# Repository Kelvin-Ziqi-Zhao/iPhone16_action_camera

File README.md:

# iPhone camera to IPEX coaxial cabel

Extend iPhone 16 Pro/Max wide camera FPC, using IPEX 20454 20pin

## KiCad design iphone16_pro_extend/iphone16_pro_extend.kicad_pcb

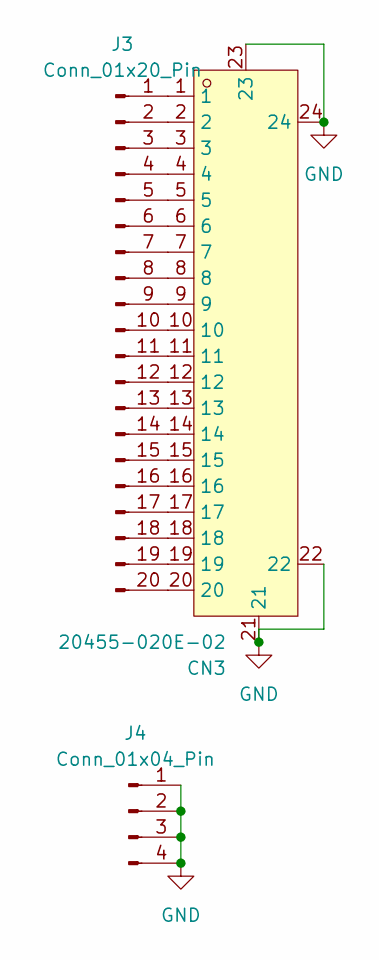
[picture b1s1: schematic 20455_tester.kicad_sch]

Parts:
CN3: 20455-020E-02; CONN-SMD_20P-P0.50_I-PEX_20455-020E-02; LCSC Part C7527729
J3: Conn_01x20_Pin; PinSocket_1x20_P2.54mm_Vertical
J4: Conn_01x04_Pin; PinSocket_1x04_P2.54mm_Vertical

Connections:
GND: CN3.21, CN3.22, CN3.23, CN3.24, J4.1, J4.2, J4.3, J4.4; also elsewhere on the board
unnamed: CN3.1, J3.1
unnamed: CN3.2, J3.2
unnamed: CN3.3, J3.3
unnamed: CN3.4, J3.4
unnamed: CN3.5, J3.5
unnamed: CN3.6, J3.6
unnamed: CN3.7, J3.7
unnamed: CN3.8, J3.8
unnamed: CN3.9, J3.9
unnamed: CN3.10, J3.10
unnamed: CN3.11, J3.11
unnamed: CN3.12, J3.12
unnamed: CN3.13, J3.13
unnamed: CN3.14, J3.14
unnamed: CN3.15, J3.15
unnamed: CN3.16, J3.16
unnamed: CN3.17, J3.17
unnamed: CN3.18, J3.18
unnamed: CN3.19, J3.19
unnamed: CN3.20, J3.20

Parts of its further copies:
CN4: 20455-020E-02; CONN-SMD_20P-P0.50_I-PEX_20455-020E-02; LCSC Part C7527729
J5: Conn_01x20_Pin; PinSocket_1x20_P2.54mm_Vertical
J6: Conn_01x04_Pin; PinSocket_1x04_P2.54mm_Vertical

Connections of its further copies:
GND: CN4.21, CN4.22, CN4.23, CN4.24, J6.1, J6.2, J6.3, J6.4; also elsewhere on the board
unnamed: CN4.1, J5.1
unnamed: CN4.2, J5.2
unnamed: CN4.3, J5.3
unnamed: CN4.4, J5.4
unnamed: CN4.5, J5.5
unnamed: CN4.6, J5.6
unnamed: CN4.7, J5.7
unnamed: CN4.8, J5.8
unnamed: CN4.9, J5.9
unnamed: CN4.10, J5.10
unnamed: CN4.11, J5.11
unnamed: CN4.12, J5.12
unnamed: CN4.13, J5.13
unnamed: CN4.14, J5.14
unnamed: CN4.15, J5.15
unnamed: CN4.16, J5.16
unnamed: CN4.17, J5.17
unnamed: CN4.18, J5.18
unnamed: CN4.19, J5.19
unnamed: CN4.20, J5.20

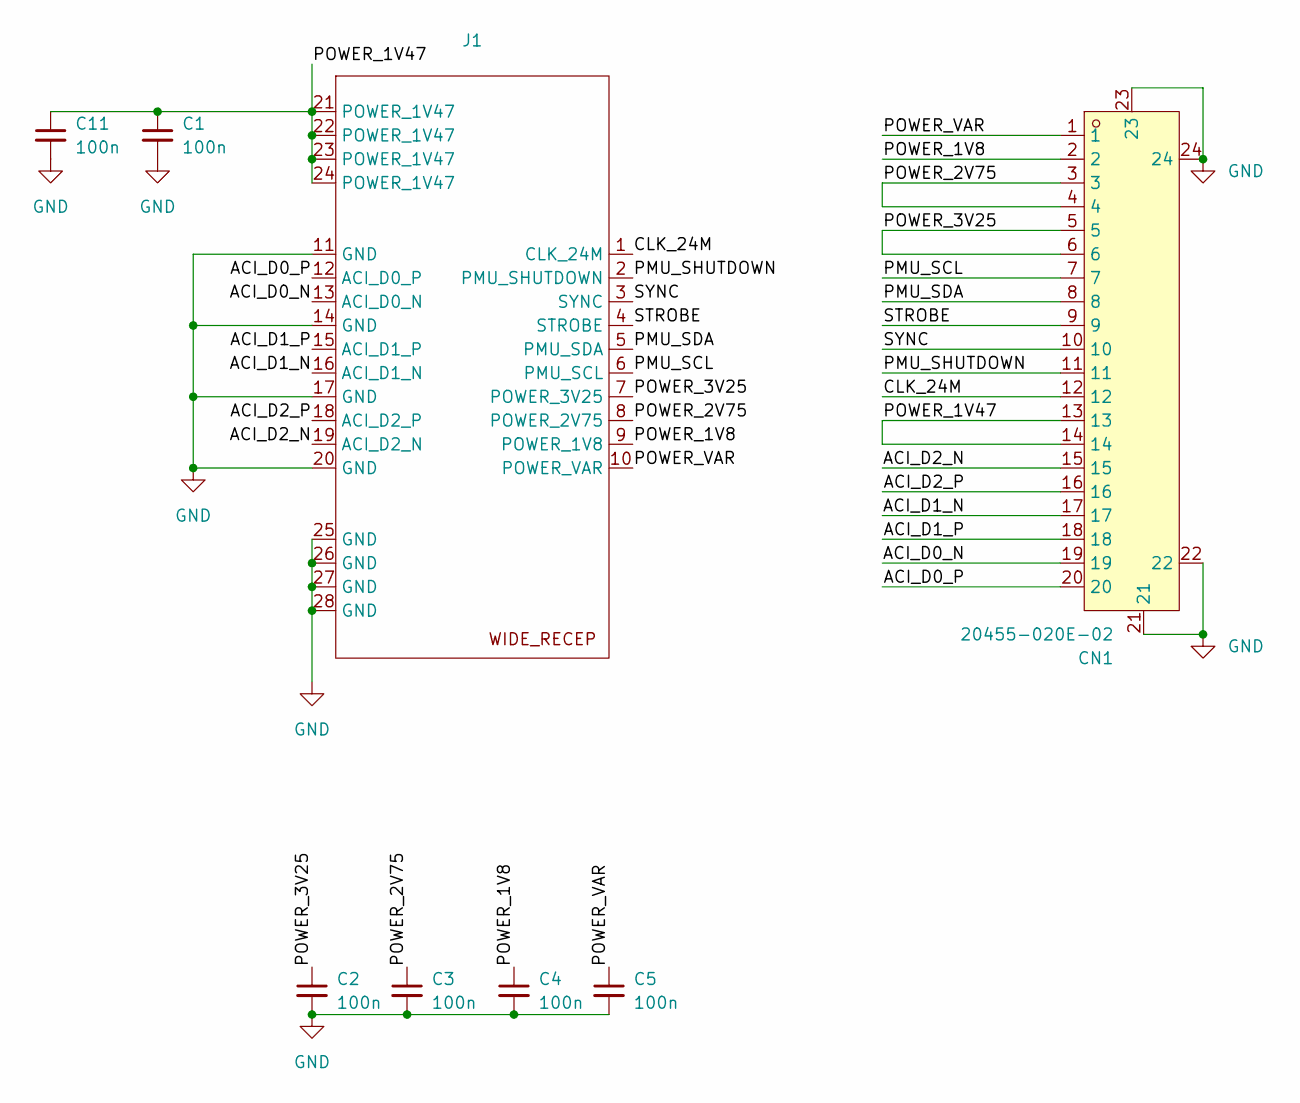
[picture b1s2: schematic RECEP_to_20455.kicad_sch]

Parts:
C1, C2, C3, C4, C5, C11: 100n; C_0603_1608Metric
CN1: 20455-020E-02; CONN-SMD_20P-P0.50_I-PEX_20455-020E-02; LCSC Part C7527729
J1: wide_camera_receptacle_J10500

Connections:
/RECEP_to_20455/ACI_D0_N: CN1.19, J1.13 (ACI_D0_N)
/RECEP_to_20455/ACI_D0_P: CN1.20, J1.12 (ACI_D0_P)
/RECEP_to_20455/ACI_D1_N: CN1.17, J1.16 (ACI_D1_N)
/RECEP_to_20455/ACI_D1_P: CN1.18, J1.15 (ACI_D1_P)
/RECEP_to_20455/ACI_D2_N: CN1.15, J1.19 (ACI_D2_N)
/RECEP_to_20455/ACI_D2_P: CN1.16, J1.18 (ACI_D2_P)
/RECEP_to_20455/CLK_24M: CN1.12, J1.1 (CLK_24M)
/RECEP_to_20455/PMU_SCL: CN1.7, J1.6 (PMU_SCL)
/RECEP_to_20455/PMU_SDA: CN1.8, J1.5 (PMU_SDA)
/RECEP_to_20455/PMU_SHUTDOWN: CN1.11, J1.2 (PMU_SHUTDOWN)
/RECEP_to_20455/POWER_1V8: C4.1, CN1.2, J1.9 (POWER_1V8)
/RECEP_to_20455/POWER_1V47: C1.1, C11.1, CN1.13, CN1.14, J1.21 (POWER_1V47), J1.22 (POWER_1V47), J1.23 (POWER_1V47), J1.24 (POWER_1V47)
/RECEP_to_20455/POWER_2V75: C3.1, CN1.3, CN1.4, J1.8 (POWER_2V75)
/RECEP_to_20455/POWER_3V25: C2.1, CN1.5, CN1.6, J1.7 (POWER_3V25)
/RECEP_to_20455/POWER_VAR: C5.1, CN1.1, J1.10 (POWER_VAR)
/RECEP_to_20455/STROBE: CN1.9, J1.4 (STROBE)
/RECEP_to_20455/SYNC: CN1.10, J1.3 (SYNC)
GND: C1.2, C2.2, C3.2, C4.2, C5.2, C11.2, CN1.21, CN1.22, CN1.23, CN1.24, J1.11 (GND), J1.14 (GND), J1.17 (GND), J1.20 (GND), J1.25 (GND), J1.26 (GND), J1.27 (GND), J1.28 (GND); also elsewhere on the board

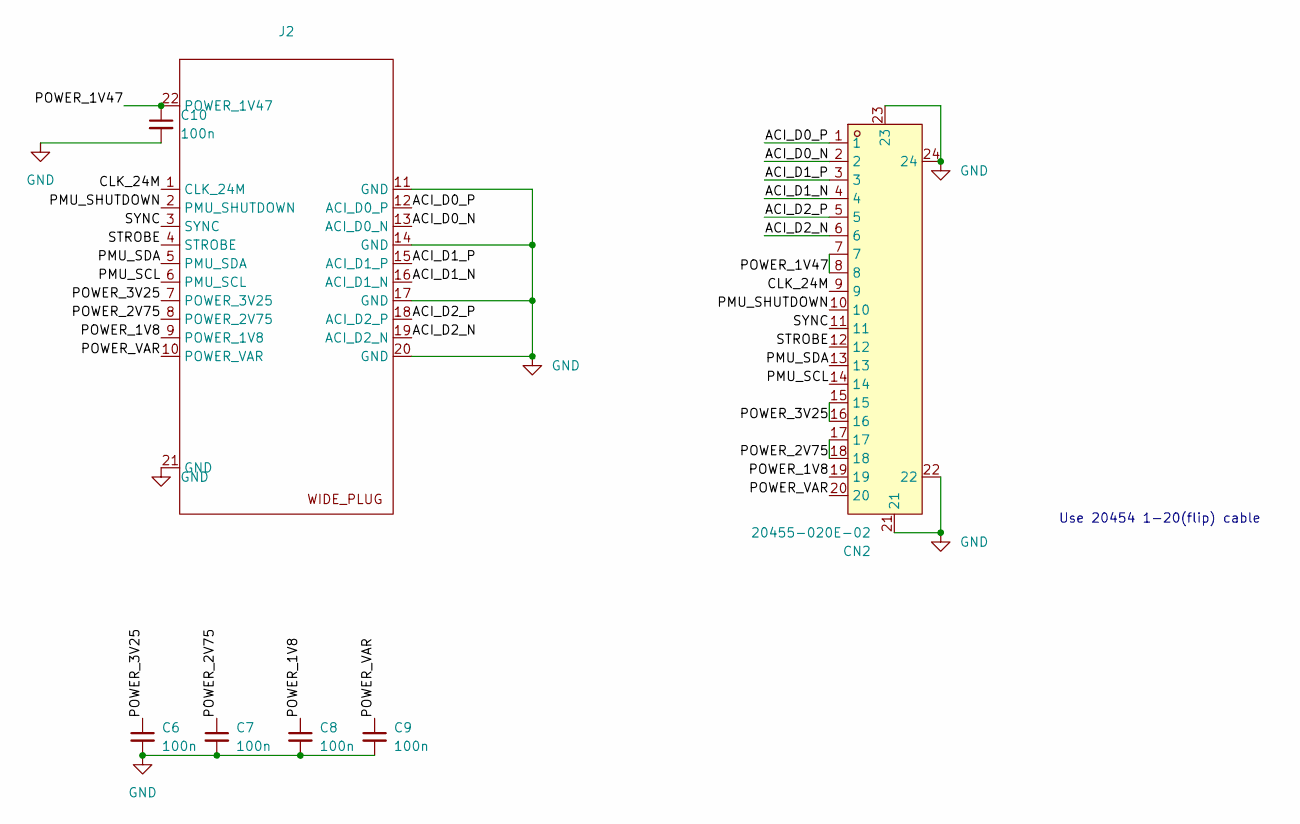
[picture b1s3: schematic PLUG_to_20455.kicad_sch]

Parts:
C6, C7, C8, C9, C10: 100n; C_0603_1608Metric
CN2: 20455-020E-02; CONN-SMD_20P-P0.50_I-PEX_20455-020E-02; LCSC Part C7527729
J2: wide_camera_plug

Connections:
/PLUG_to_20455/ACI_D0_N: CN2.2, J2.13 (ACI_D0_N)
/PLUG_to_20455/ACI_D0_P: CN2.1, J2.12 (ACI_D0_P)
/PLUG_to_20455/ACI_D1_N: CN2.4, J2.16 (ACI_D1_N)
/PLUG_to_20455/ACI_D1_P: CN2.3, J2.15 (ACI_D1_P)
/PLUG_to_20455/ACI_D2_N: CN2.6, J2.19 (ACI_D2_N)
/PLUG_to_20455/ACI_D2_P: CN2.5, J2.18 (ACI_D2_P)
/PLUG_to_20455/CLK_24M: CN2.9, J2.1 (CLK_24M)
/PLUG_to_20455/PMU_SCL: CN2.14, J2.6 (PMU_SCL)
/PLUG_to_20455/PMU_SDA: CN2.13, J2.5 (PMU_SDA)
/PLUG_to_20455/PMU_SHUTDOWN: CN2.10, J2.2 (PMU_SHUTDOWN)
/PLUG_to_20455/POWER_1V8: C8.1, CN2.19, J2.9 (POWER_1V8)
/PLUG_to_20455/POWER_1V47: C10.1, CN2.7, CN2.8, J2.22 (POWER_1V47)
/PLUG_to_20455/POWER_2V75: C7.1, CN2.17, CN2.18, J2.8 (POWER_2V75)
/PLUG_to_20455/POWER_3V25: C6.1, CN2.15, CN2.16, J2.7 (POWER_3V25)
/PLUG_to_20455/POWER_VAR: C9.1, CN2.20, J2.10 (POWER_VAR)
/PLUG_to_20455/STROBE: CN2.12, J2.4 (STROBE)
/PLUG_to_20455/SYNC: CN2.11, J2.3 (SYNC)
GND: C6.2, C7.2, C8.2, C9.2, C10.2, CN2.21, CN2.22, CN2.23, CN2.24, J2.11 (GND), J2.14 (GND), J2.17 (GND), J2.20 (GND), J2.21 (GND); also elsewhere on the board

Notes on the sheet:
Use 20454 1-20(flip) cable

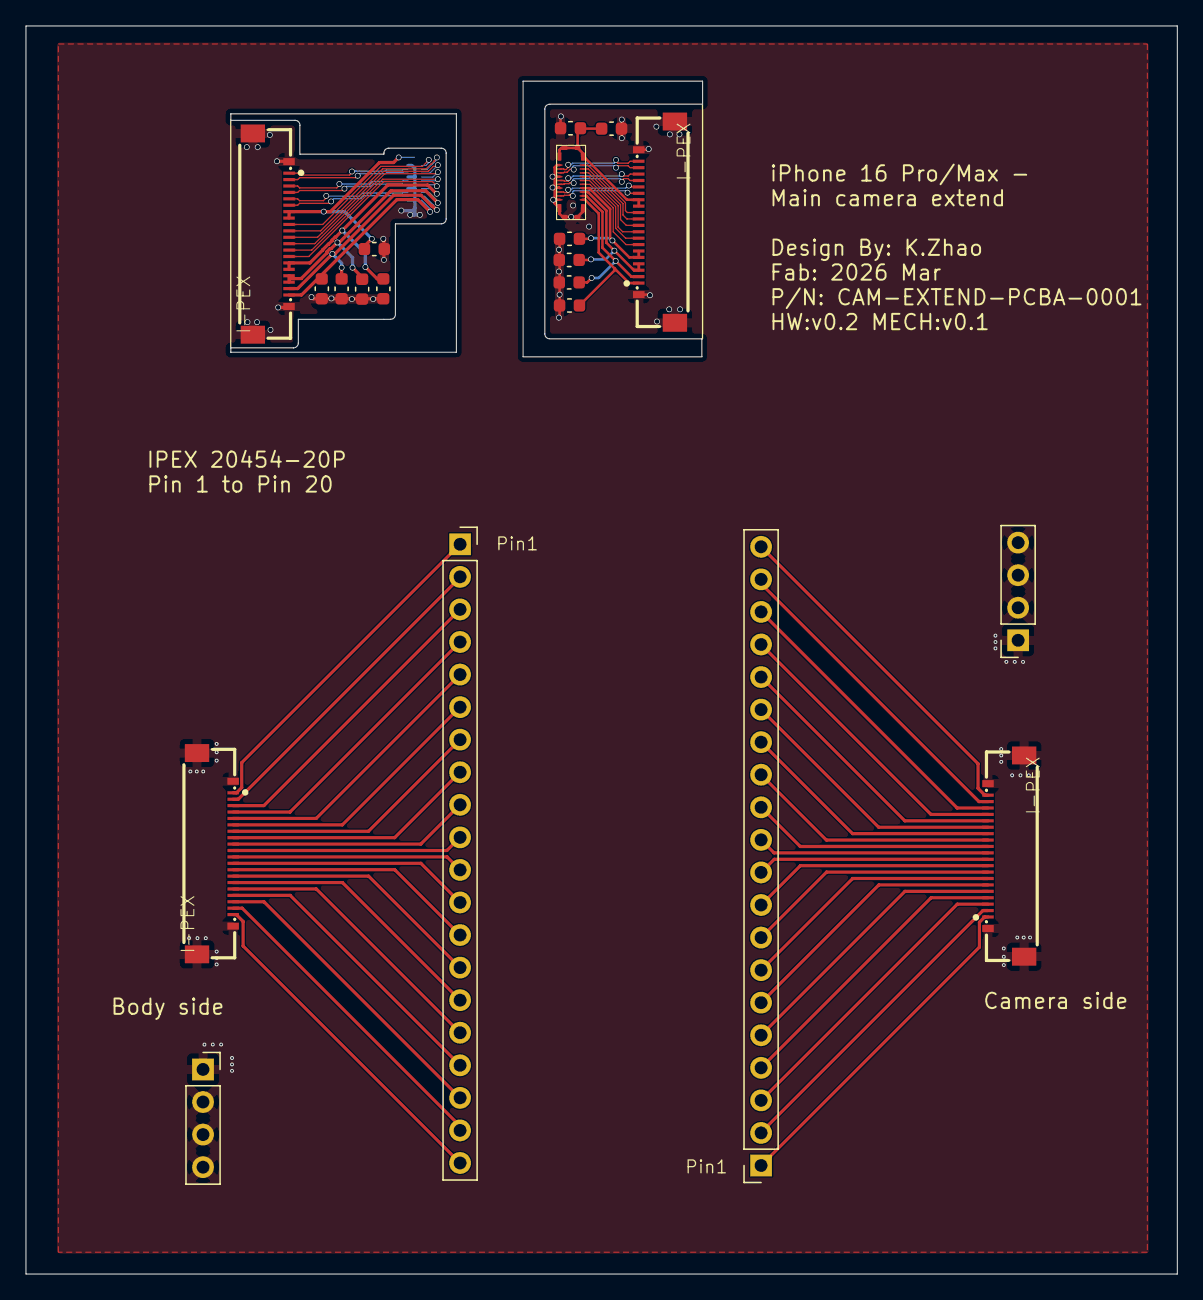
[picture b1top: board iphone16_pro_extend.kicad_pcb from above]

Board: 4 copper layers, 89.8 x 97.4 mm, 21 parts (1 on the bottom side), 75 nets.

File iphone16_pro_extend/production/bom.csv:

Designator,Footprint,Quantity,Value,LCSC Part #
"C1, C10, C11, C2, C3, C4, C5, C6, C7, C8, C9",0603,11,100n,
"CN1, CN2, CN3, CN4",CONN-SMD_20P-P0.50_I-PEX_20455-020E-02,4,20455-020E-02,C7527729
J1,wide_camera_receptacle_J10500,1,~,
J2,wide_camera_plug,1,~,
"J3, J5",PinSocket_1x20_P2.54mm_Vertical,2,Conn_01x20_Pin,
"J4, J6",PinSocket_1x04_P2.54mm_Vertical,2,Conn_01x04_Pin,

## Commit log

2026-03-25 Change via diameter to 0.3/0.4mm, reroute
2026-03-25 Change via holes to 0.35/0.45
2026-03-25 first production file
